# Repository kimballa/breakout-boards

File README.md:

SMD breakout boards
===================

This repo contains Kicad projects and camera-ready gerber files for panelized SMD component breakout boards.
The design of these breakout boards emphasizes narrow breakouts that "waste" fewer rows of pins in breadboards,
at the expense of slightly longer breakout boards that "overhang"  some number of pins to the left or right
of the actual pin header. In most cases, breakout boards are the same width as a comparable THT DIP
component. Others span the gap in the middle of a breadboard plus only a single extra row (beyond the two rows
necessary for the pin headers).

Panels are designed to fit within the 100x100 mm size for a JLCPCB economy "special price" build. In many
cases, the 5 panel minimum will still result in a supply of breakout boards that will last even ambitious
hobbyists a long while. If you require more, the low marginal cost of increasing to 10 or 20 panels likely 
outcompetes the cost of making larger panels that can be ordered at qty=5.

Directory structure
-------------------

There are a few subdirectories that each contain one or more breakout boards:

* `soic` - Two panels with a mix of SOIC-8, -14, and -16 breakouts, and TSSOP-8, -14, and -16
  breakouts.
* `soic-dw` - A panel with a mix of "widebody" (Texas Instruments drawing "DW") SOIC-16 and
  SOIC-20 breakouts
* `sot-23` - Two panels of SOT-23-6 and SOT-23-8 breakouts
* `qfn-20` - A non-panelized QFN-20 breakout board
* `so-8-fet` - Panelized SO-8 / 5050 FET / Power-TDFN footprint for SMD power MOSFETs.
  Uses NXP's "universal 5060 footprint" for maximum adaptability.
* `micromatch-20` - a separate (non-panelized) breakout for the MicroMaTcH 20 pin connector 

All panels were created with KiKit. Each "base" directory contains Kicad project and PCB layout(s)
for singleton breakout boards. Panelized PCBs are in a subdirectory called `out` or `panelized`.

* The SOT-23 and SO-8-FET breakout boards were made using the KiKit GUI from the plugin. To regenerate, load the JSON config
  file to load the appropriate settings, and identify the input kicad_pcb and target kicad_pcb files.
* The SOIC / TSSOP and SOIC-DW breakout boards were made using the KiKit API. Each directory has a script
  called `panelize.py`. Open a KiCad Command Line terminal and run `python panelize.py` in the directory.
  The output will be generated in the `out/` subdirectory. The same `panelize.py` script in the `soic` 
  directory is used for generating SOIC or TSSOP panel, but some settings at the top of the script must
  be edited to switch from one to the other.

Gerber files are available in the `rtm/` subdirectory of each subproject. If multiple subdirectories exist
within `rtm`, choose the highest-numbered version to get the latest Gerbers.

Ordering breakout panels
------------------------

Zip up the gerber (and .drl) files in a given rtm directory and upload it to JLCPCB.com. The panel size and "2 layers" 
should be auto-selected. Choose "panel by customer", input the number of unique designs in the board file
(3 for SOIC and TSSOP; 2 for SOIC-DW, 1 for SOT-23-6 and SOT-23-8), and the number of rows and columns.

You should also probably select "remove order number", and your choice of HASL or HASL Lead-free surface
finishing. (You could choose ENIG but it will be overkill, *unless you are ordering the QFN*, in which case
it is mandatory.)

The default number of each panel you order is 5; you can also dial this up as-needed. 

Assembly
--------

Arrange your SMT component on the board with pin 1 closest to the dot or triangular arrow mark on the board
in the SMT area. Tack down one pin with your soldering iron, then do the rest. Clip pin headers to length
and place them in the breadboard, then seat the breakout board on top. Solder from above, lightly pressing 
the board down onto the seating plane of the pin headers.  

Any 2.54mm-pitch pin headers will do, but if you're looking for a specific part to order, Amphenol ICC (FCI)
part number `68000-400HLF` is a quality cuttable pin header strip, orderable from Mouser, Digikey, and likely
many others. Order qty is the number of connected pins you'd like; I typically buy by the 500 or so.

Where possible, a "ground plane" is provided on many breakout boards. A separate 1.1mm hole is available
in the middle of the board. After attaching the chip and the pin headers, solder a short piece of jumper 
wire from the hole to the top of whichever pin indicates GND (likely the one in the front right corner, 
but not always; check your datasheet).

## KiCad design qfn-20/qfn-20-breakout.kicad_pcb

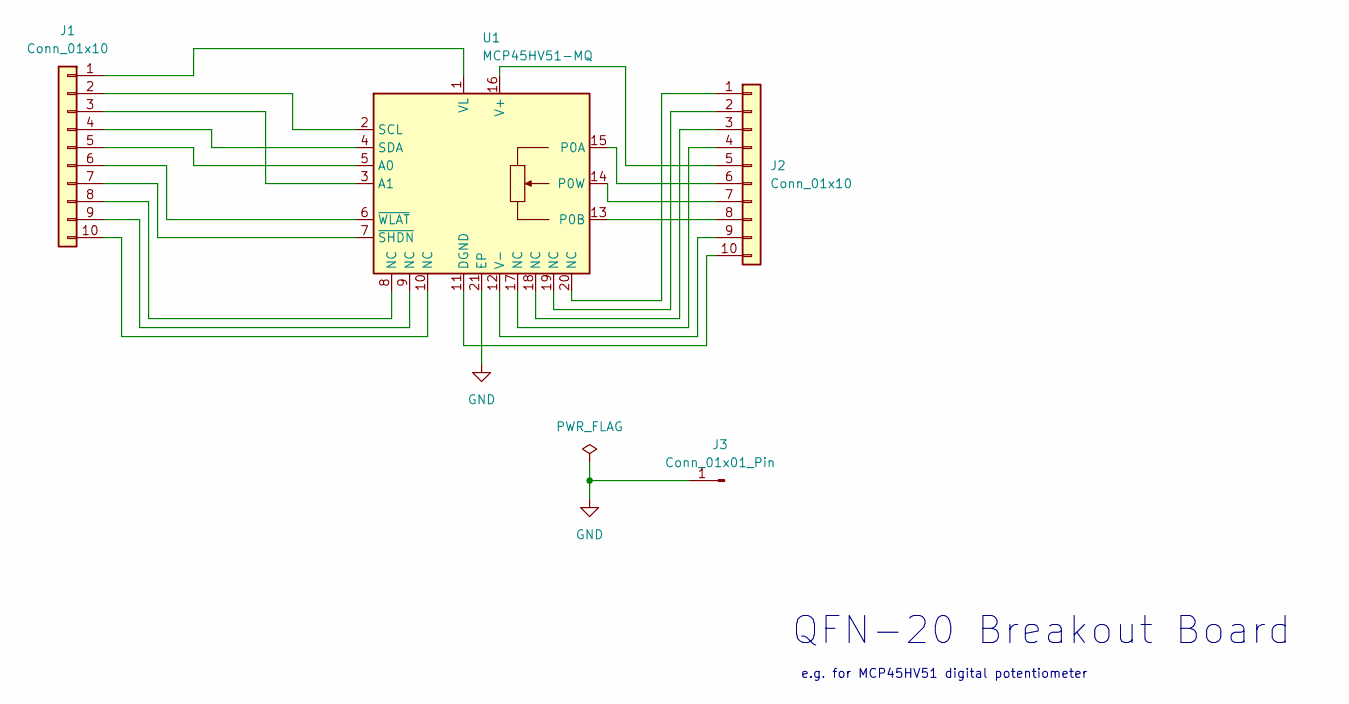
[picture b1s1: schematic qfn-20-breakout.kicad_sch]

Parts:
J1, J2: Conn_01x10; PinHeader_1x10_P2.54mm_Vertical
J3: Conn_01x01_Pin; TP_HeaderPin_P2.54mm_round
U1: MCP45HV51-MQ; TI-QFN-20-1EP_5x5mm_P0.65mm_EP3.35x3.35mm

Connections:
GND: J3.1, U1.21 (EP)
unnamed: J1.1, U1.1 (VL)
unnamed: J1.2, U1.2 (SCL)
unnamed: J1.3, U1.3 (A1)
unnamed: J1.4, U1.4 (SDA)
unnamed: J1.5, U1.5 (A0)
unnamed: J1.6, U1.6 (~WLAT)
unnamed: J1.7, U1.7 (~SHDN)
unnamed: J1.8, U1.8 (NC)
unnamed: J1.9, U1.9 (NC)
unnamed: J1.10, U1.10 (NC)
unnamed: J2.1, U1.20 (NC)
unnamed: J2.2, U1.19 (NC)
unnamed: J2.3, U1.18 (NC)
unnamed: J2.4, U1.17 (NC)
unnamed: J2.5, U1.16 (V+)
unnamed: J2.6, U1.15 (P0A)
unnamed: J2.7, U1.14 (P0W)
unnamed: J2.8, U1.13 (P0B)
unnamed: J2.9, U1.12 (V-)
unnamed: J2.10, U1.11 (DGND)

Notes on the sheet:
e.g. for MCP45HV51 digital potentiometer
QFN-20 Breakout Board

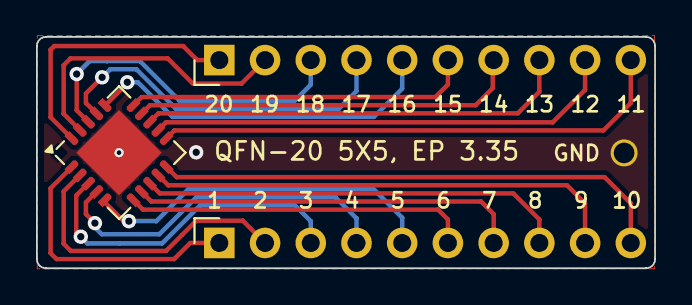
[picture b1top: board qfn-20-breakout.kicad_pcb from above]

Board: 2 copper layers, 34.3 x 12.9 mm, 4 parts (0 on the bottom side), 21 nets.

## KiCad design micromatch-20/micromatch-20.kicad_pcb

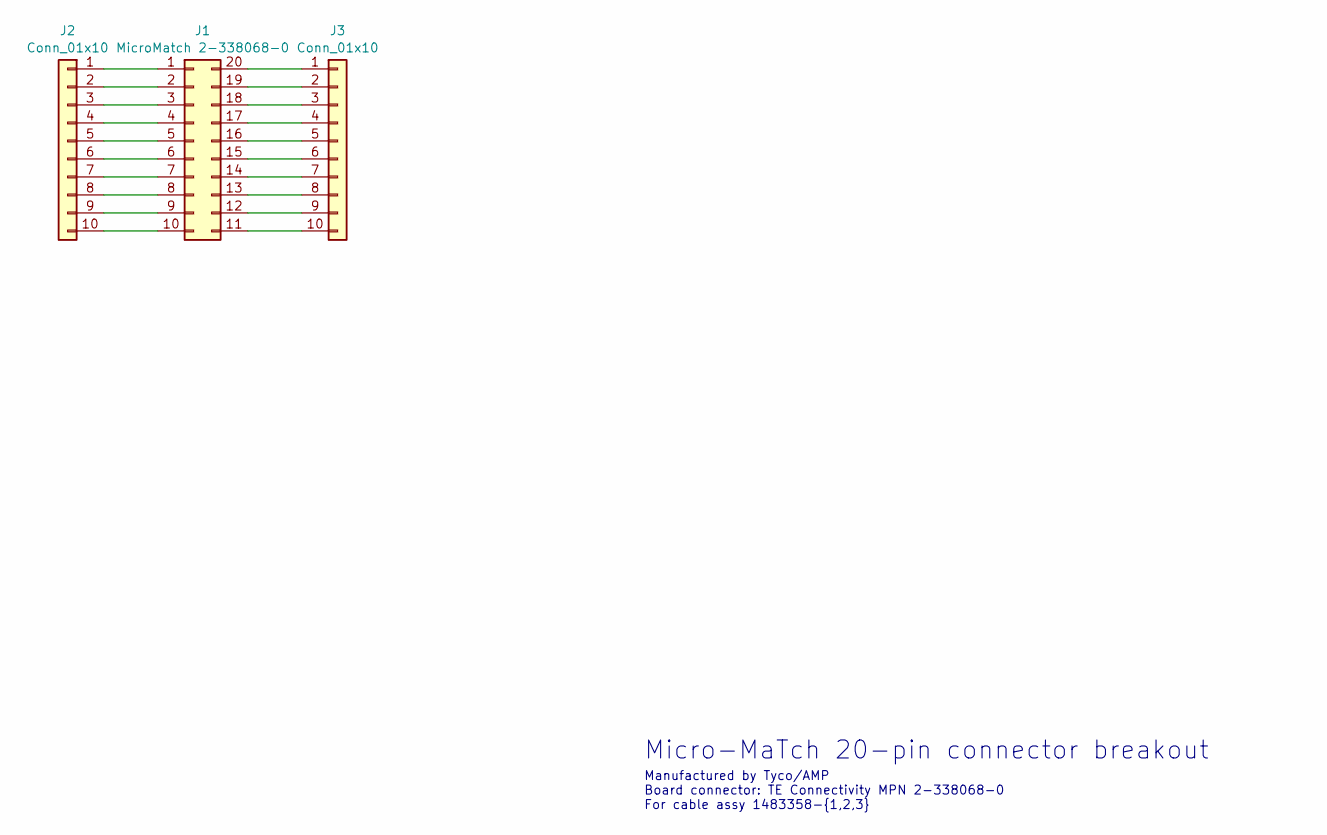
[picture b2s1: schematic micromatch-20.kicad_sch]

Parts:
J1: MicroMatch 2-338068-0; MicroMatch_20_F_Socket_2x10
J2, J3: Conn_01x10; PinHeader_1x10_P2.54mm_Vertical

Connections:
unnamed: J1.1, J2.1
unnamed: J1.2, J2.2
unnamed: J1.3, J2.3
unnamed: J1.4, J2.4
unnamed: J1.5, J2.5
unnamed: J1.6, J2.6
unnamed: J1.7, J2.7
unnamed: J1.8, J2.8
unnamed: J1.9, J2.9
unnamed: J1.10, J2.10
unnamed: J1.11, J3.10
unnamed: J1.12, J3.9
unnamed: J1.13, J3.8
unnamed: J1.14, J3.7
unnamed: J1.15, J3.6
unnamed: J1.16, J3.5
unnamed: J1.17, J3.4
unnamed: J1.18, J3.3
unnamed: J1.19, J3.2
unnamed: J1.20, J3.1

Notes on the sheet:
Micro-MaTch 20-pin connector breakout
Manufactured by Tyco/AMP Board connector: TE Connectivity MPN 2-338068-0 For cable assy 1483358-{1,2,3}

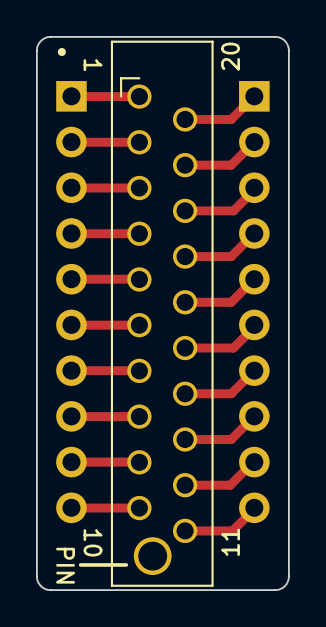
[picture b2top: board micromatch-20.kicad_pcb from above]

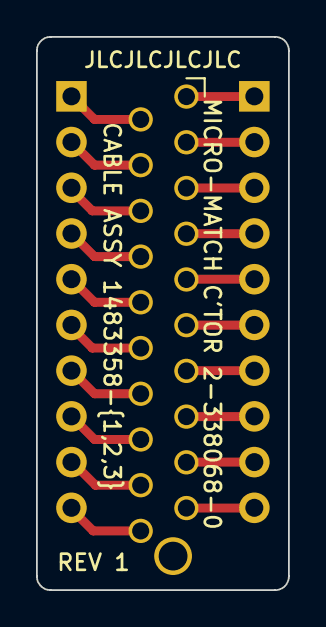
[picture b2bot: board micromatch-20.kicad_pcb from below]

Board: 2 copper layers, 14.0 x 30.7 mm, 3 parts (2 on the bottom side), 20 nets.

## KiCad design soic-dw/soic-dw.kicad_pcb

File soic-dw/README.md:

SOIC-DW (Wide) Breakouts
========================

Breakout boards for {16, 20}-pin wide-body SOIC (1.27mm pitch) ICs that fit in standard pin
alignment on a breadboard.

The IC itself sits to the side of the pin headers rather than between them, to achieve a
narrow breakout board profile (12.8mm) that straddles only one extra row of pins on one
or the other side of the breadboard centerline.

A separate through-hole exists in the SOIC-16 board, connected to the ground plane. Solder a
resistor leg or other thin wire from the `GND` hole to top of the header pin that
represents ground for the IC. (Or leave floating if there is no appropriate ground pin for
the IC.)

The file name (SOIC-DW) derives from Texas Instruments' name for the wide SOIC package type.

## Gerber files

The latest gerber files for submitting to a board fab are in the `rtm/` directory.

If submitting to JLCPCB, select 'panel by customer', 'number of designs' = 2.

## Panelization

The main project file includes one of each representative breakout board. Panels with 8x
SOIC-16 and 6x SOIC-20 format were generated using KiKit. If you change the main PCB
CAD file, you should then open a KiCad Command Prompt in this directory and run `python
panelize.py`. You can edit `panelize.py` first to set variables related to the output file
to generate.

### Script notes:

The current layout is intended to fit in the 100x100 mm area that offers the best
deal for JLCPCB, but you can extend taller or wider if desired.

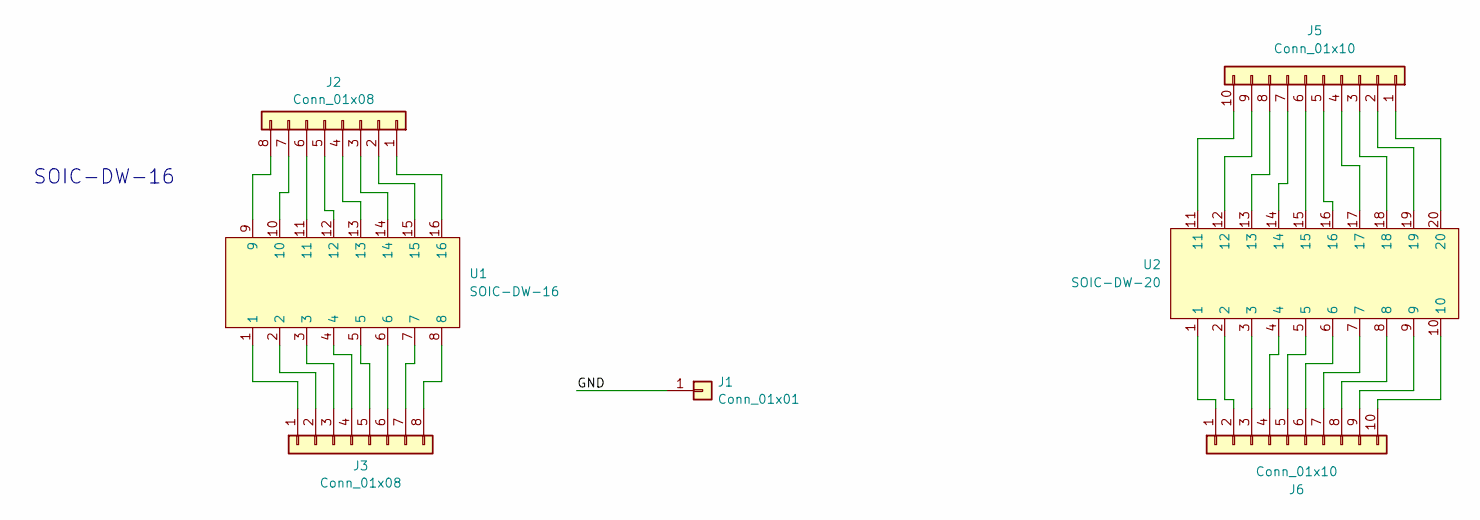
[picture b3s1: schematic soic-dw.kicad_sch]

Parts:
J1: Conn_01x01; TP_HeaderPin_P2.54mm_round
J2, J3: Conn_01x08; PinHeader_1x08_P2.54mm_Vertical
J5, J6: Conn_01x10; PinHeader_1x10_P2.54mm_Vertical
U1: SOIC-DW-16; TI_SOIC_DW0016A_MinSilk
U2: SOIC-DW-20; TI_SOIC_DW0020A

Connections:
/GND: J1.1
unnamed: J2.1, U1.16
unnamed: J2.2, U1.15
unnamed: J2.3, U1.14
unnamed: J2.4, U1.13
unnamed: J2.5, U1.12
unnamed: J2.6, U1.11
unnamed: J2.7, U1.10
unnamed: J2.8, U1.9
unnamed: J3.1, U1.1
unnamed: J3.2, U1.2
unnamed: J3.3, U1.3
unnamed: J3.4, U1.4
unnamed: J3.5, U1.5
unnamed: J3.6, U1.6
unnamed: J3.7, U1.7
unnamed: J3.8, U1.8
unnamed: J5.1, U2.20
unnamed: J5.2, U2.19
unnamed: J5.3, U2.18
unnamed: J5.4, U2.17
unnamed: J5.5, U2.16
unnamed: J5.6, U2.15
unnamed: J5.7, U2.14
unnamed: J5.8, U2.13
unnamed: J5.9, U2.12
unnamed: J5.10, U2.11
unnamed: J6.1, U2.1
unnamed: J6.2, U2.2
unnamed: J6.3, U2.3
unnamed: J6.4, U2.4
unnamed: J6.5, U2.5
unnamed: J6.6, U2.6
unnamed: J6.7, U2.7
unnamed: J6.8, U2.8
unnamed: J6.9, U2.9
unnamed: J6.10, U2.10

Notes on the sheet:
SOIC-DW-16

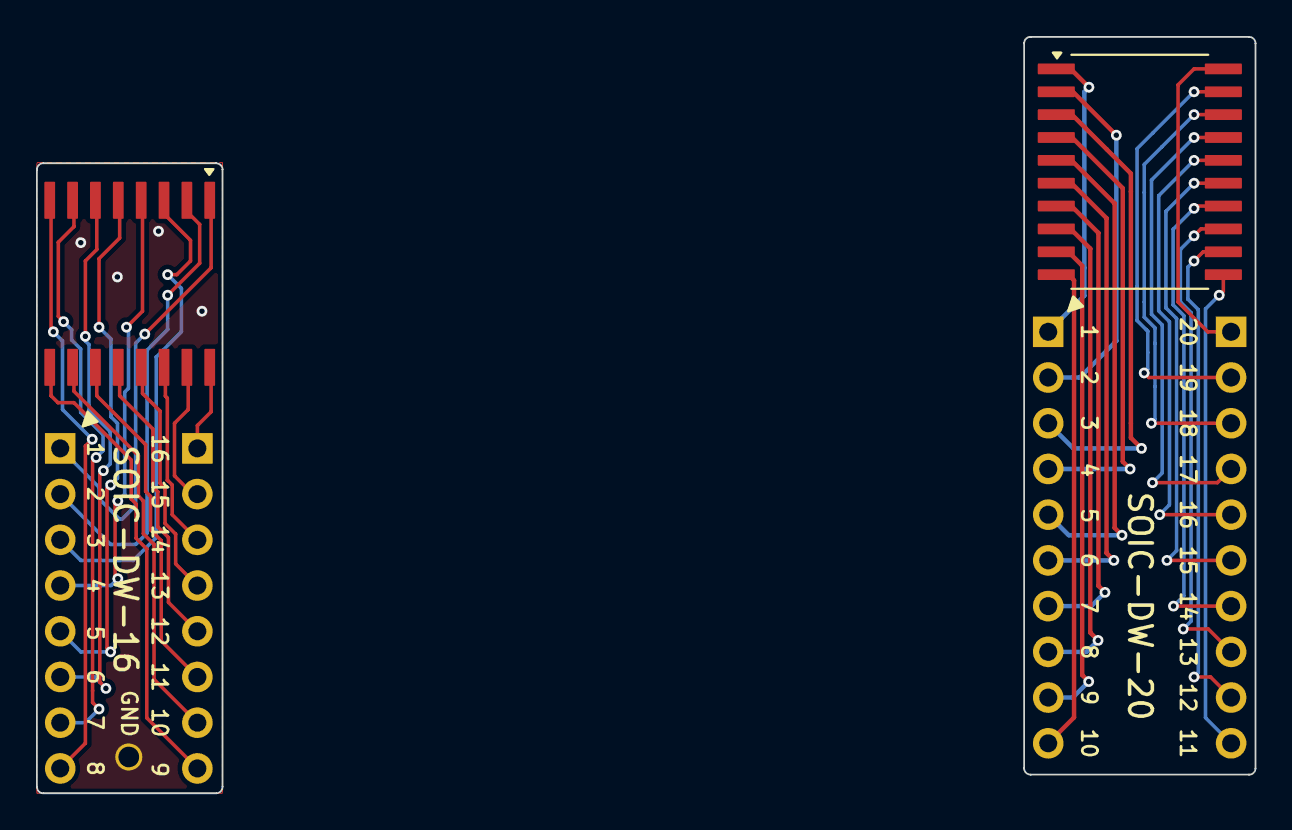
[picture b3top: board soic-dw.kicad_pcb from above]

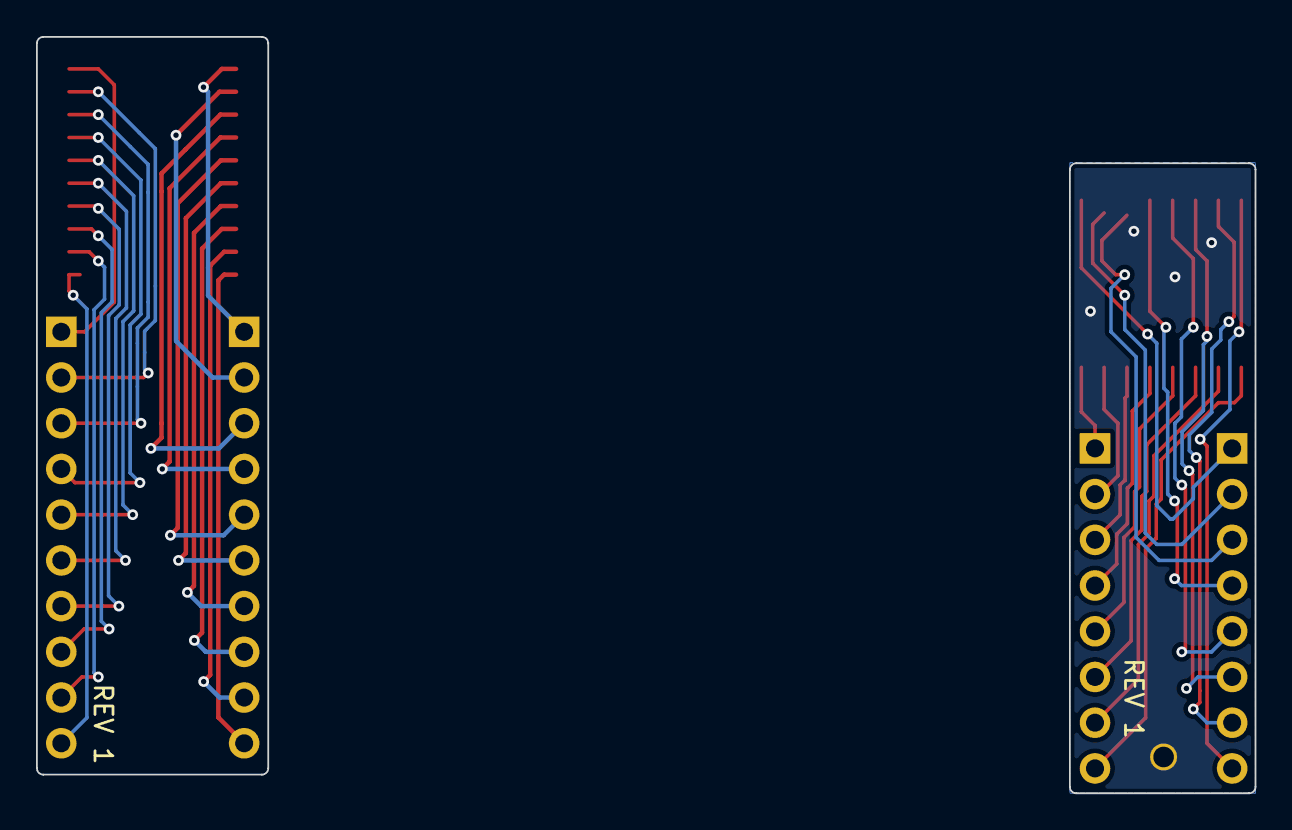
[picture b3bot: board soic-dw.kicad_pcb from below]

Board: 2 copper layers, 67.7 x 42.0 mm, 9 parts (4 on the bottom side), 36 nets.

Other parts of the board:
B1, B2: Board

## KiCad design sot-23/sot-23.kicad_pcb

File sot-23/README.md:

SOT-23 breakouts
================

This directory contains kicad project files and camera-ready gerber files for SOT-23-6 and
SOT-23-8 breakout board PCBs.

Order PCBs
----------

Look in the `panelized/rtm/` directory and select the subdirectory with the highest
version number.  There are separate subdirectories in there for SOT-23-6 and SOT-23-8
breakout boards. Take all the files in one of those subdirectories (gerber files and
Excellon drill files) and zip them together. 

Order PCBs from jlcpcb.com:
* upload the zip file
* Set PCB Qty as you desire
* Panel By Customer
  * SOT-23-6: 10 cols, 6 rows
  * SOT-23-8: 7 cols, 6 rows
* Surface Finish: HASL (with lead) or LeadFree HASL as you desire
* All other options as-default.

To adjust board layouts
-----------------------

There is a source schematic which was used to create the sot-23 (6) and sot-23-8 kicad_pcb
files.  The schematic contains both breakouts; half of this was deleted on each PCB,
leaving each kicad_pcb file with a single sot-23-6 or sot-23-8 breakout. 

The panel PCBs in the `panelized/` subdirectory were derived from these using the KiKit
panelization plugin. JSON config files for each board are in the panelized/ directory and
can be imported into the KiKit configuration dialog to reproduce the same settings used to
generate the current panels.

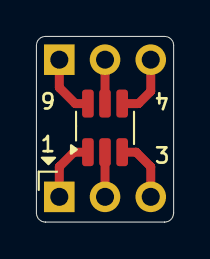
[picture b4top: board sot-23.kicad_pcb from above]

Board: 2 copper layers, 7.6 x 10.3 mm, 3 parts (0 on the bottom side), 6 nets.

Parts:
J1, J2: Conn_01x03; PinHeader_1x03_P2.54mm_Vertical
Q1: BCM847DS; SOT-23-6_Handsoldering

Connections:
unnamed: J1.1, Q1.1 (E1)
unnamed: J1.2, Q1.2 (B1)
unnamed: J1.3, Q1.3 (C2)
unnamed: J2.1, Q1.6 (C1)
unnamed: J2.2, Q1.5 (B2)
unnamed: J2.3, Q1.4 (E2)

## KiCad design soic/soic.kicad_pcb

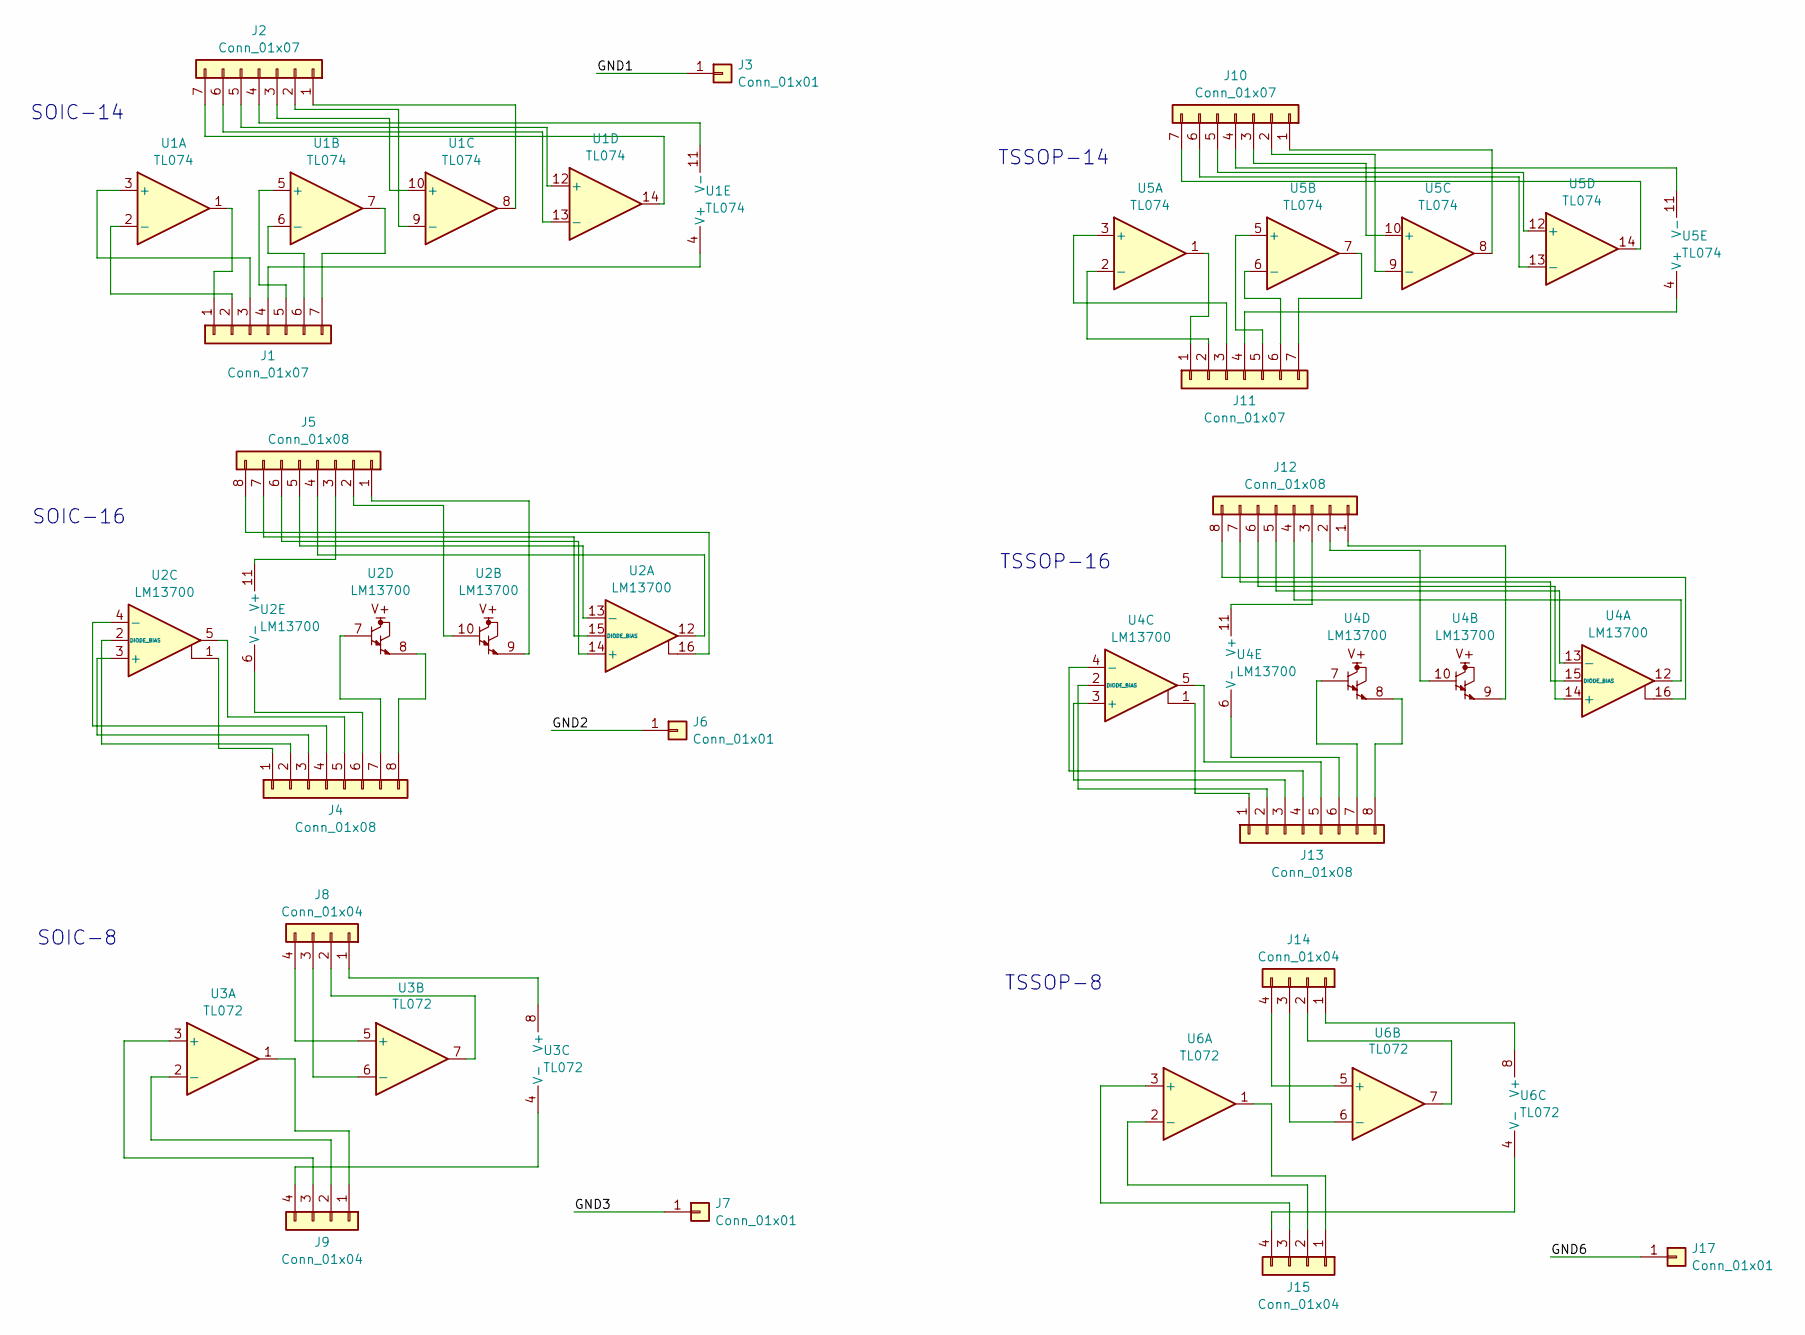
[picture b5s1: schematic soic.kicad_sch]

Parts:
J1, J2, J10, J11: Conn_01x07; PinHeader_1x07_P2.54mm_Vertical
J3, J6, J7, J17: Conn_01x01; TP_HeaderPin_P2.54mm_round
J4, J5, J12, J13: Conn_01x08; PinHeader_1x08_P2.54mm_Vertical
J8, J9, J14, J15: Conn_01x04; PinHeader_1x04_P2.54mm_Vertical
U1: TL074; TI_SOIC_D_R-PDSO-G14
U2: LM13700; TI_SOIC_D_R-PDSO-16
U3: TL072; TI_SOIC_D_R-PDSO-8
U4: LM13700; TSSOP-16_4.4x5mm_P0.65mm
U5: TL074; TI_TSSOP_PW0014A
U6: TL072; TI_TSSOP_PW0008A

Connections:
/GND1: J3.1
/GND2: J6.1
/GND3: J7.1
/GND6: J17.1
unnamed: J1.1, U1.1
unnamed: J1.2, U1.2 (-)
unnamed: J1.3, U1.3 (+)
unnamed: J1.4, U1.4 (V+)
unnamed: J1.5, U1.5 (+)
unnamed: J1.6, U1.6 (-)
unnamed: J1.7, U1.7
unnamed: J2.1, U1.8
unnamed: J2.2, U1.9 (-)
unnamed: J2.3, U1.10 (+)
unnamed: J2.4, U1.11 (V-)
unnamed: J2.5, U1.12 (+)
unnamed: J2.6, U1.13 (-)
unnamed: J2.7, U1.14
unnamed: J4.1, U2.1
unnamed: J4.2, U2.2 (DIODE_BIAS)
unnamed: J4.3, U2.3 (+)
unnamed: J4.4, U2.4 (-)
unnamed: J4.5, U2.5
unnamed: J4.6, U2.6 (V-)
unnamed: J4.7, U2.7
unnamed: J4.8, U2.8
unnamed: J5.1, U2.9
unnamed: J5.2, U2.10
unnamed: J5.3, U2.11 (V+)
unnamed: J5.4, U2.12
unnamed: J5.5, U2.13 (-)
unnamed: J5.6, U2.14 (+)
unnamed: J5.7, U2.15 (DIODE_BIAS)
unnamed: J5.8, U2.16
unnamed: J8.1, U3.8 (V+)
unnamed: J8.2, U3.7
unnamed: J8.3, U3.6 (-)
unnamed: J8.4, U3.5 (+)
unnamed: J9.1, U3.1
unnamed: J9.2, U3.2 (-)
unnamed: J9.3, U3.3 (+)
unnamed: J9.4, U3.4 (V-)
unnamed: J10.1, U5.8
unnamed: J10.2, U5.9 (-)
unnamed: J10.3, U5.10 (+)
unnamed: J10.4, U5.11 (V-)
unnamed: J10.5, U5.12 (+)
unnamed: J10.6, U5.13 (-)
unnamed: J10.7, U5.14
unnamed: J11.1, U5.1
unnamed: J11.2, U5.2 (-)
unnamed: J11.3, U5.3 (+)
unnamed: J11.4, U5.4 (V+)
unnamed: J11.5, U5.5 (+)
unnamed: J11.6, U5.6 (-)
unnamed: J11.7, U5.7
unnamed: J12.1, U4.9
unnamed: J12.2, U4.10
unnamed: J12.3, U4.11 (V+)
unnamed: J12.4, U4.12
unnamed: J12.5, U4.13 (-)
unnamed: J12.6, U4.14 (+)
unnamed: J12.7, U4.15 (DIODE_BIAS)
unnamed: J12.8, U4.16
unnamed: J13.1, U4.1
unnamed: J13.2, U4.2 (DIODE_BIAS)
unnamed: J13.3, U4.3 (+)
unnamed: J13.4, U4.4 (-)
unnamed: J13.5, U4.5
unnamed: J13.6, U4.6 (V-)
unnamed: J13.7, U4.7
unnamed: J13.8, U4.8
unnamed: J14.1, U6.8 (V+)
unnamed: J14.2, U6.7
unnamed: J14.3, U6.6 (-)
unnamed: J14.4, U6.5 (+)
unnamed: J15.1, U6.1
unnamed: J15.2, U6.2 (-)
unnamed: J15.3, U6.3 (+)
unnamed: J15.4, U6.4 (V-)

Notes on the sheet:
SOIC-14
TSSOP-8
SOIC-8
TSSOP-14
SOIC-16
TSSOP-16

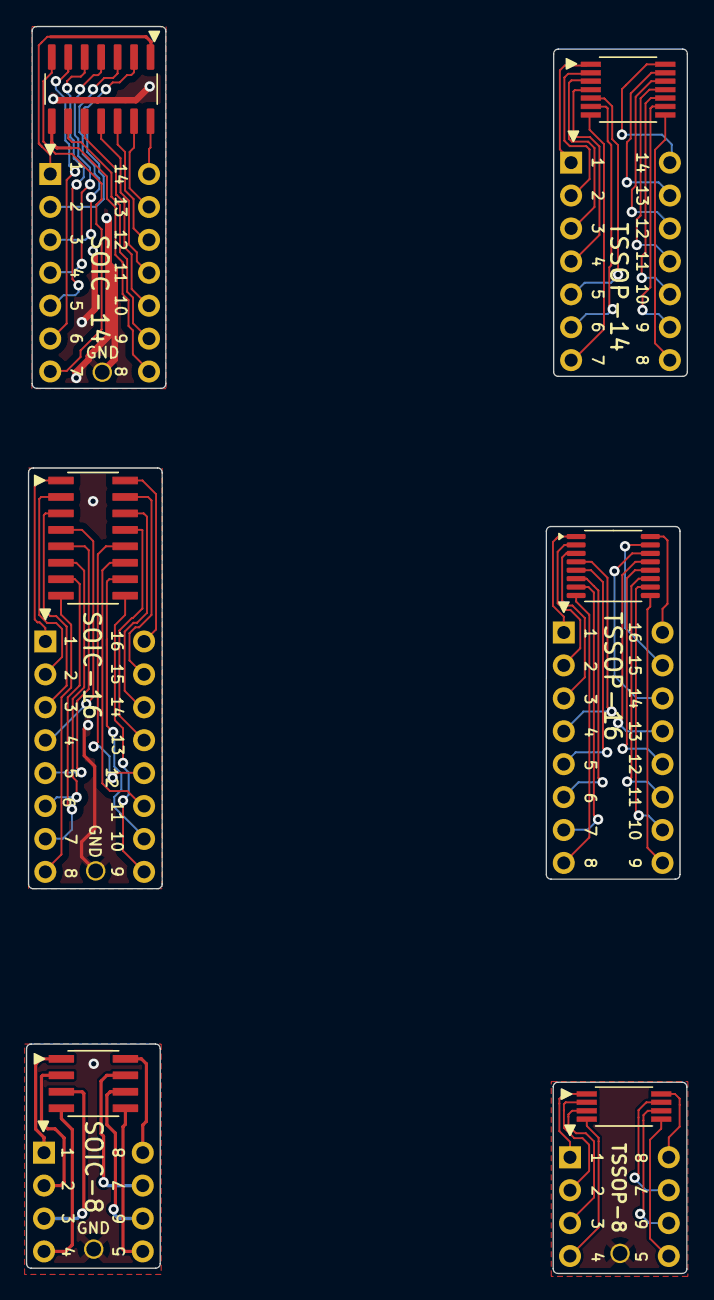
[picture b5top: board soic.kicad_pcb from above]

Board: 2 copper layers, 51.0 x 96.2 mm, 28 parts (0 on the bottom side), 76 nets.

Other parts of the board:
B1, B2, B3, B4, B5, B6: Board
